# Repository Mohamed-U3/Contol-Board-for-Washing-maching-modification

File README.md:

# Contol-Board-for-Washing-maching-modification

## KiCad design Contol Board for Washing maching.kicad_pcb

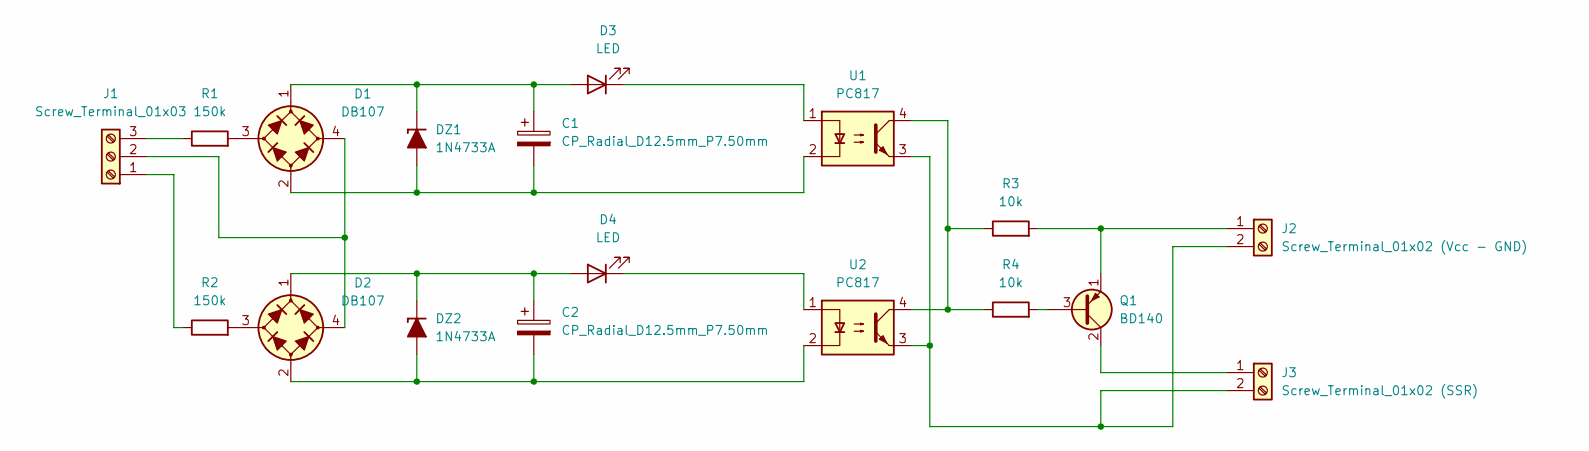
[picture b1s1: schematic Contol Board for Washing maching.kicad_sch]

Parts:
C1, C2: CP_Radial_D12.5mm_P7.50mm
D1, D2: DB107; Diode_Bridge_DIP-4_W7.62mm_P5.08mm
D3, D4: LED; LED_D3.0mm
DZ1, DZ2: 1N4733A; D_DO-41_SOD81_P10.16mm_Horizontal_Zener
J1: Screw_Terminal_01x03; TerminalBlock_Phoenix_MKDS-1,5-3_1x03_P5.00mm_Horizontal
J2: Screw_Terminal_01x02 (Vcc - GND); TerminalBlock_Phoenix_MKDS-1,5-2_1x02_P5.00mm_Horizontal
J3: Screw_Terminal_01x02 (SSR); TerminalBlock_Phoenix_MKDS-1,5-2_1x02_P5.00mm_Horizontal
Q1: BD140; TO-126-3_Vertical_ECB
R1, R2: 150k; R_Axial_DIN0207_L6.3mm_D2.5mm_P10.16mm_Horizontal
R3, R4: 10k; R_Axial_DIN0204_L3.6mm_D1.6mm_P7.62mm_Horizontal
U1, U2: PC817; DIP-4_W7.62mm

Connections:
unnamed: D1.3 (1), R1.2
unnamed: D1.4 (2), D2.4 (2), J1.2
unnamed: C1.1, D1.1 (+), D3.2 (A), DZ1.1 (K)
unnamed: C1.2, D1.2 (-), DZ1.2 (A), U1.2
unnamed: D2.3 (1), R2.2
unnamed: C2.1, D2.1 (+), D4.2 (A), DZ2.1 (K)
unnamed: C2.2, D2.2 (-), DZ2.2 (A), U2.2
unnamed: D3.1 (K), U1.1
unnamed: D4.1 (K), U2.1
unnamed: J1.1, R2.1
unnamed: J1.3, R1.1
unnamed: J2.1, Q1.1 (E), R3.2
unnamed: J2.2, J3.2, U1.3, U2.3
unnamed: J3.1, Q1.2 (C)
unnamed: Q1.3 (B), R4.2
unnamed: R3.1, R4.1, U1.4, U2.4

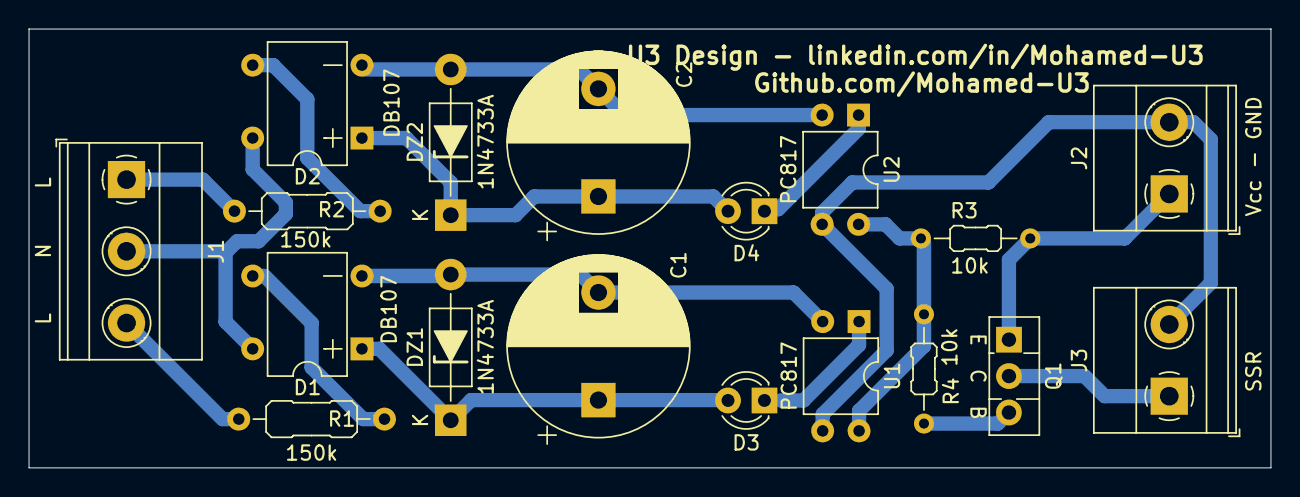
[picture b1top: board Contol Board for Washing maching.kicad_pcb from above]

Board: 2 copper layers, 86.6 x 30.6 mm, 18 parts (0 on the bottom side), 16 nets.

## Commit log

2025-08-26 First commit.. this board if manufactured as prototype and it's working.
